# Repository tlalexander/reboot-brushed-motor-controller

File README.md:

Brushed Motor Controller by Taylor Alexander from reboot.love

NOTICE: I would love it if someone wanted to manufacture these for their own profit. I have licensed everything CC0 which means I release all rights. I just want someone to make these! The current design works but can be improved. If anyone wants to produce these, please email me and we can collaborate on improving the design.

Purpose:

There are lots of low cost (under $10) brushed gear motors with encoders on Aliexpress and Amazon. This board is designed to precisely drive those motors, using encoder feedback and current measurement for precise positioning, velocity, and current control.

Possible improvements:
Q1 is a little small physically.
Form factor could be improved.
J1, J10, J11 could be removed, along with Q3.
Should check motor pinouts and compare to common motors.

License Notes:
This board is heavily modified from David Grubb's Jaguar-USB-tap.
https://github.com/dgrubb/Jaguar-USB-tap
That board has a GPL license. When I emailed David for permission to relicense as CC0, he replied "I don't think you need my permission."
So I am relicensing CC0 as I tend to prefer that type of license. If you have any concerns over licensing, contact David Grubb or consider following the more restrictive GPL V3.0 License (meaning: share your modifications and everything will be fine).

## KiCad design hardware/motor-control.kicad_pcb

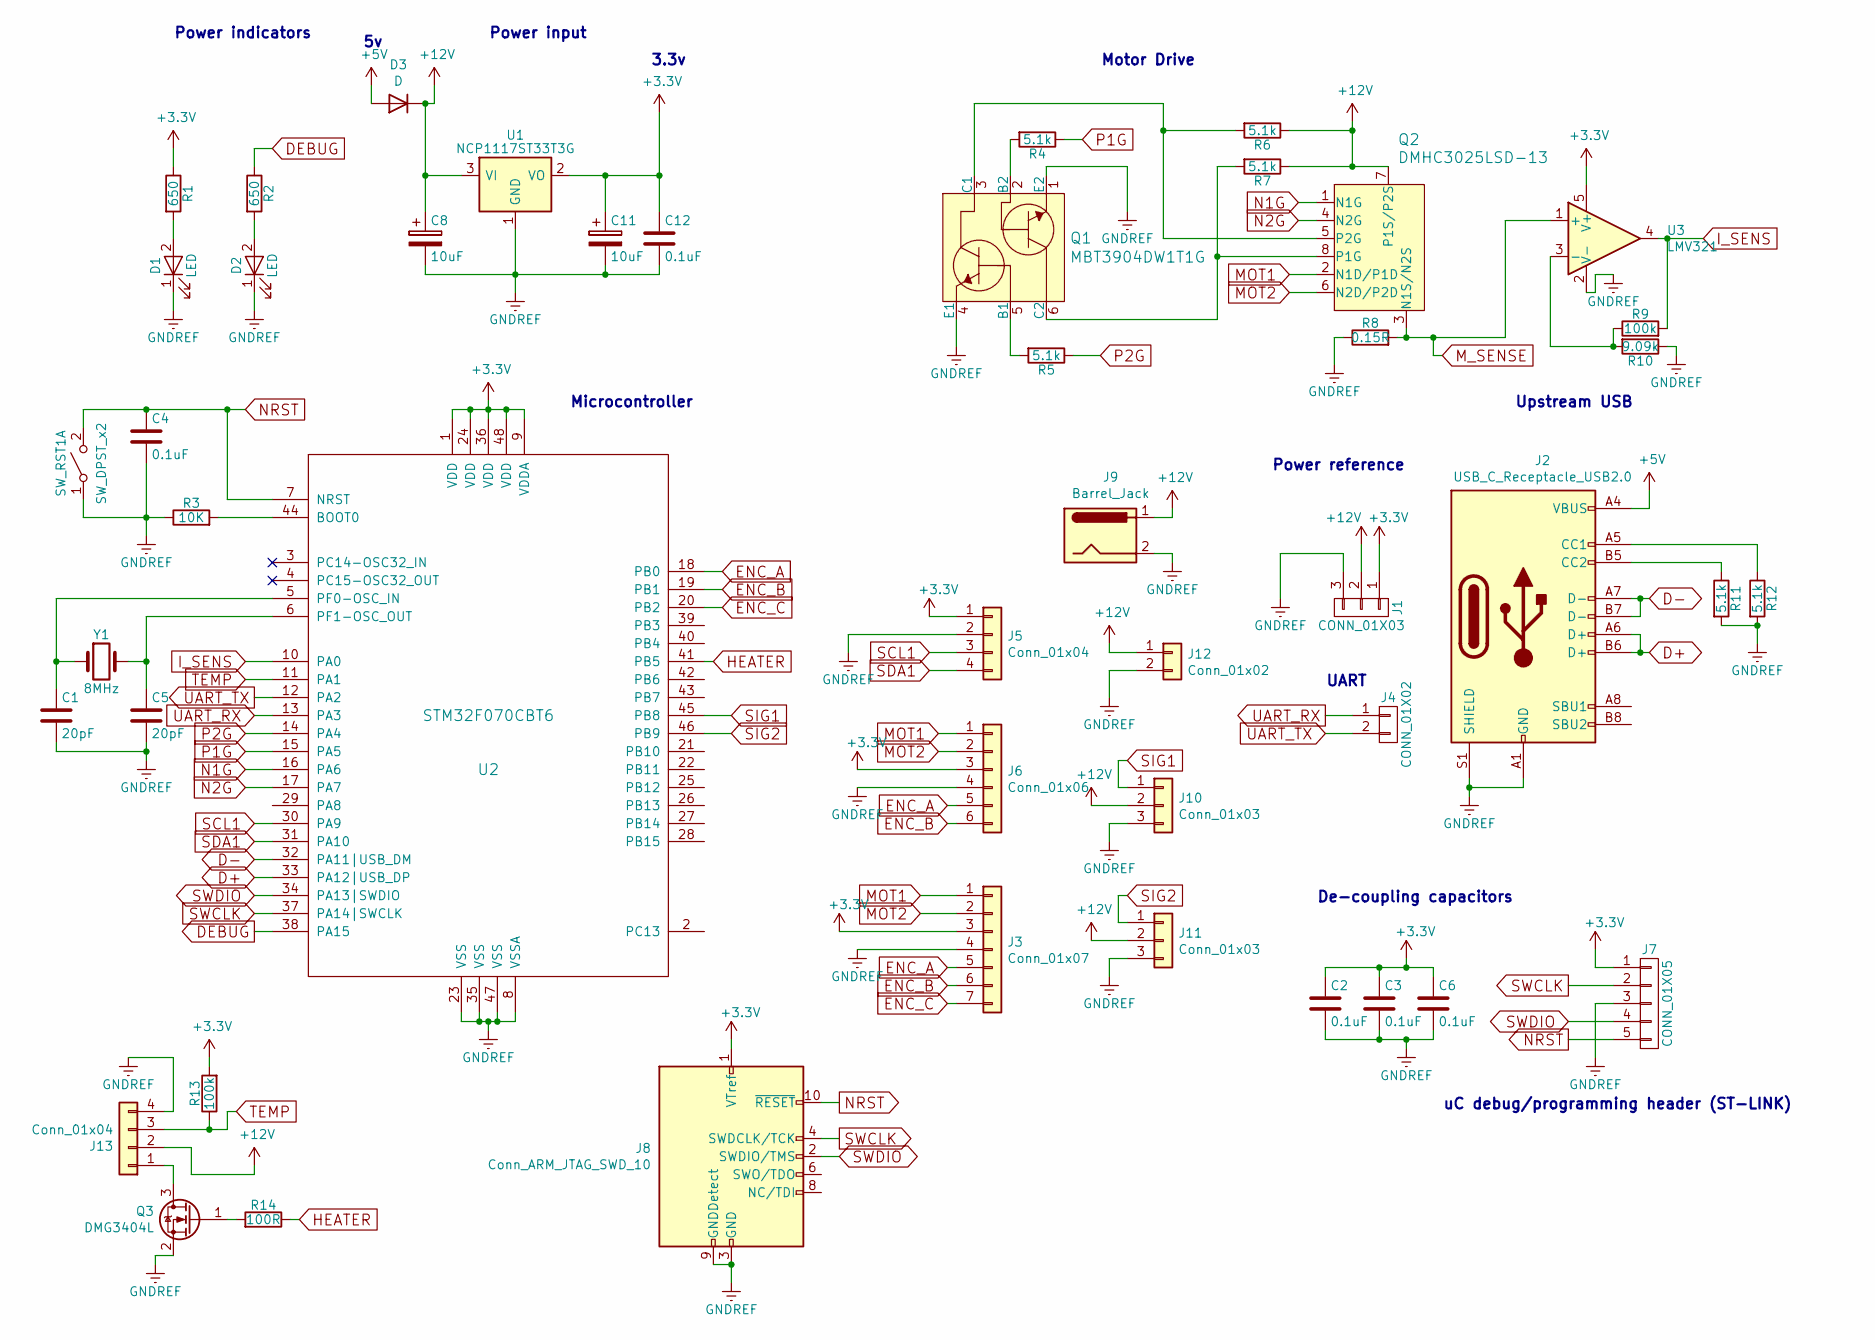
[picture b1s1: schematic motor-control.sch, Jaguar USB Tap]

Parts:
C1, C5: 20pF; C_0805_2012Metric
C2, C3, C4, C6, C12: 0.1uF; C_0805_2012Metric
C8, C11: 10uF; C_1210_3225Metric
D1, D2: LED; LED_1206
D3: D; D_1210_3225Metric
J1: CONN_01X03; Pin_Header_Straight_1x03_Pitch2.54mm
J2: USB_C_Receptacle_USB2.0; USB_C_Receptacle_GCT_USB4085
J3: Conn_01x07; PinHeader_1x07_P2.54mm_Vertical
J4: CONN_01X02; PinHeader_1x02_P2.54mm_Vertical
J5, J13: Conn_01x04; PinHeader_1x04_P2.54mm_Vertical
J6: Conn_01x06; JST_PH_B6B-PH-K_1x06_P2.00mm_Vertical
J7: CONN_01X05; PinHeader_1x05_P2.54mm_Vertical
J8: Conn_ARM_JTAG_SWD_10; SAMTEC_FTSH-105-01-L-DV-K
J9: Barrel_Jack; BarrelJack_CUI_PJ-063AH_Horizontal
J10, J11: Conn_01x03; PinHeader_1x03_P2.54mm_Vertical
J12: Conn_01x02; PinHeader_1x02_P2.54mm_Vertical
Q1: MBT3904DW1T1G; SOT-363; MPN MBT3904DW1T1G; Digi-Key_PN MBT3904DW1T1GOSCT-ND
Q2: DMHC3025LSD-13; SOIC-8_W3.9mm; MPN DMHC3025LSD-13; Digi-Key_PN DMHC3025LSD-13DICT-ND
Q3: DMG3404L; SOT-23
R1, R2: 650; R_0805_2012Metric
R3: 10K; R_0805_2012Metric
R4, R5, R6, R7, R11, R12: 5.1k; R_0805_2012Metric
R8: 0.15R; R_2512_6332Metric
R9, R13: 100k; R_0805_2012Metric
R10: 9.09k; R_0805_2012Metric
R14: 100R; R_0805_2012Metric
SW_RST1: SW_DPST_x2; Panasonic_EVQPUK_EVQPUB
U1: NCP1117ST33T3G; SOT-223
U2: STM32F070CBT6; LQFP-48_7x7mm_Pitch0.5mm
U3: LMV321; SOT-23-5
Y1: 8MHz; Crystal_SMD_5032-2Pin_5.0x3.2mm

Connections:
+3V3: C2.1, C3.1, C6.1, C11.1, C12.1, J1.1, J3.3, J5.1, J6.3, J7.1, J8.1 (VTref), R1.1, R13.2, U1.2 (VO), U2.1 (VDD), U2.9 (VDDA), U2.24 (VDD), U2.36 (VDD), U2.48 (VDD), U3.5 (V+)
+5V: D3.2 (A), J2.A4 (VBUS), J2.A9 (VBUS), J2.B4 (VBUS), J2.B9 (VBUS)
+12V: C8.1, D3.1 (K), J1.2, J9.1, J10.2, J11.2, J12.1, J13.2, Q2.7 (P1S/P2S), R6.1, R7.1, U1.3 (VI)
D+: J2.A6 (D+), J2.B6 (D+), U2.33 (PA12|USB_DP)
D-: J2.A7 (D-), J2.B7 (D-), U2.32 (PA11|USB_DM)
DEBUG: R2.1, U2.38 (PA15)
ENC_A: J3.5, J6.5, U2.18 (PB0)
ENC_B: J3.6, J6.6, U2.19 (PB1)
ENC_C: J3.7, U2.20 (PB2)
GNDREF: C1.2, C2.2, C3.2, C4.2, C5.2, C6.2, C8.2, C11.2, C12.2, D1.1 (K), D2.1 (K), J1.3, J2.A1 (GND), J2.A12 (GND), J2.B1 (GND), J2.B12 (GND), J2.S1 (SHIELD), J3.4, J5.2, J6.4, J7.3, J8.3 (GND), J8.5 (GND), J8.9 (GNDDetect), J9.2, J10.3, J11.3, J12.2, J13.4, Q1.1 (E2), Q1.4 (E1), Q3.2 (S), R3.1, R8.1, R10.1, R11.2, R12.2, SW_RST1.1 (A), U1.1 (GND), U2.8 (VSSA), U2.23 (VSS), U2.35 (VSS), U2.47 (VSS), U3.2 (V-)
HEATER: R14.1, U2.41 (PB5)
I_SENS: R9.2, U2.10 (PA0), U3.4
MOT1: J3.1, J6.1, Q2.2 (N1D/P1D)
MOT2: J3.2, J6.2, Q2.6 (N2D/P2D)
M_SENSE: Q2.3 (N1S/N2S), R8.2, U3.1 (+)
N1G: Q2.1 (N1G), U2.16 (PA6)
N2G: Q2.4 (N2G), U2.17 (PA7)
NRST: C4.1, J7.5, J8.10 (~RESET~), SW_RST1.2 (B), U2.7 (NRST)
unnamed: C1.1, U2.5 (PF0-OSC_IN), Y1.1
unnamed: C5.1, U2.6 (PF1-OSC_OUT), Y1.2
unnamed: D1.2 (A), R1.2
unnamed: D2.2 (A), R2.2
unnamed: J2.A5 (CC1), R12.1
unnamed: J2.B5 (CC2), R11.1
unnamed: J13.1, Q3.3 (D)
unnamed: Q1.2 (B2), R4.2
unnamed: Q1.3 (C1), Q2.5 (P2G), R6.2
unnamed: Q1.5 (B1), R5.2
unnamed: Q1.6 (C2), Q2.8 (P1G~), R7.2
unnamed: Q3.1 (G), R14.2
unnamed: R3.2, U2.44 (BOOT0)
unnamed: R9.1, R10.2, U3.3 (-)
P1G: R5.1, U2.14 (PA4)
P2G: R4.1, U2.15 (PA5)
SCL1: J5.3, U2.30 (PA9)
SDA1: J5.4, U2.31 (PA10)
SIG1: J10.1, U2.45 (PB8)
SIG2: J11.1, U2.46 (PB9)
SWCLK: J7.2, J8.4 (SWDCLK/TCK), U2.37 (PA14|SWCLK)
SWDIO: J7.4, J8.2 (SWDIO/TMS), U2.34 (PA13|SWDIO)
TEMP: J13.3, R13.1, U2.11 (PA1)
UART_RX: J4.1, U2.13 (PA3)
UART_TX: J4.2, U2.12 (PA2)

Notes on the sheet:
Power indicators
Power input
3.3v
Power reference
Upstream USB
uC debug/programming header (ST-LINK)
UART
De-coupling capacitors
Microcontroller
Motor Drive

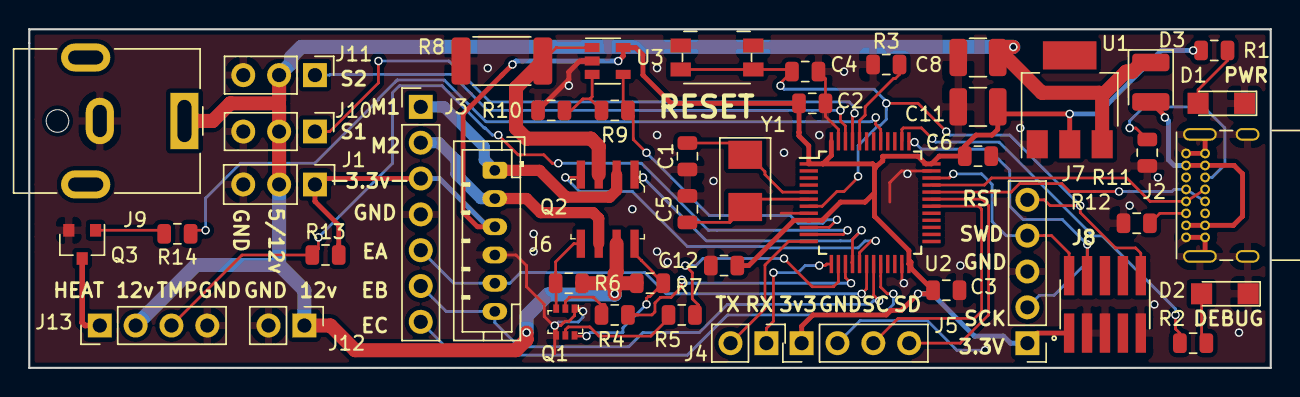
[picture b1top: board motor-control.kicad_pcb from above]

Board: 2 copper layers, 88.0 x 24.0 mm, 47 parts (0 on the bottom side), 43 nets.

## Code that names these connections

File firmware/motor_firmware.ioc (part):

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Mcu.Name=STM32F070CBTx
Mcu.Package=LQFP48
Mcu.UserName=STM32F070CBTx
PA0.Mode=IN0
PA0.Signal=ADC_IN0
PA10.Mode=Asynchronous
PA10.Signal=USART1_RX
PA11.Mode=Device
PA11.Signal=USB_DM
PA12.Mode=Device
PA12.Signal=USB_DP
PA15.GPIOParameters=PinState
PA15.PinState=GPIO_PIN_SET
PA15.Signal=GPIO_Output
PA4.Signal=GPIO_Output
PA5.Signal=GPIO_Output
PA6.Signal=S_TIM3_CH1
PA7.Signal=S_TIM3_CH2
PA9.Mode=Asynchronous
PA9.Signal=USART1_TX
PB0.GPIOParameters=GPIO_PuPd,GPIO_Label
PB0.GPIO_Label=ENC_A
PB0.GPIO_PuPd=GPIO_PULLUP
PB0.Signal=GPXTI0
PB1.GPIOParameters=GPIO_PuPd,GPIO_Label
PB1.GPIO_Label=ENC_B
PB1.GPIO_PuPd=GPIO_PULLUP
PB1.Signal=GPXTI1
PB2.GPIOParameters=GPIO_PuPd,GPIO_Label
PB2.GPIO_Label=ENC_C
PB2.GPIO_PuPd=GPIO_PULLUP
PB2.Signal=GPXTI2
PB5.Signal=GPIO_Output
PF0-OSC_IN.Mode=HSE-External-Oscillator
PF0-OSC_IN.Signal=RCC_OSC_IN
PF1-OSC_OUT.Mode=HSE-External-Oscillator
PF1-OSC_OUT.Signal=RCC_OSC_OUT
RCC.SYSCLKFreq_VALUE=48000000
RCC.SYSCLKSource=RCC_SYSCLKSOURCE_PLLCLK
board=custom

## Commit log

2021-05-05 motor controller initial commit
